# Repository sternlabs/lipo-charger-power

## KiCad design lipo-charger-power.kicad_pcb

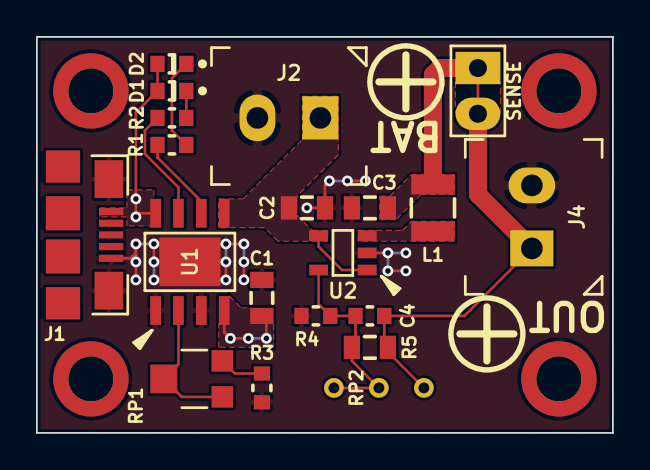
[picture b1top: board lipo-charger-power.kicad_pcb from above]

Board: 2 copper layers, 32.0 x 22.0 mm, 24 parts (0 on the bottom side), 12 nets.

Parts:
C1, C2, C3: 10u; SMD-2012
C4: 18p; SMD-1608
D1: CHRG; SMD-1608-LED
D2: STDBY; SMD-1608-LED
J1: USB-MICROB; USB-MICRO-B-FCI-10118192
J2: BAT; TERM-2-3.5-PTH
J3: SENSE; HEADER-1x2
J4: VREG; TERM-2-3.5-PTH
L1: 2.2u; SMD-2520
MH1, MH2, MH3, MH4: MOUNTHOLE; HOLE-M2.5-COND
R1, R2: 1k; SMD-1608
R3: 1k 1%; SMD-1608
R4: 255k 1%; SMD-1608
R5: 1.15M 1%; SMD-2012
RP1: 20k 25%; SMD-POT-3831
RP2: 2M 10%; POT-3296W
U1: TP4056; SOIC-8-N-EP
U2: NCP1529; SOT-23-5

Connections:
/BAT: C2.1, J2.1, U1.5, U2.1, U2.4
/VREG: C3.1, C4.2, J3.1, J3.2, J4.1, L1.2, R5.1, RP2.1
/VUSB: C1.1, D1.A, D2.A, J1.1, U1.4, U1.8
unnamed: C4.1, R4.1, R5.2, RP2.3, RP2.WIPE, U2.5
unnamed: D1.C, R2.1
unnamed: D2.C, R1.1
unnamed: L1.1, U2.3
unnamed: R1.2, U1.6
unnamed: R2.2, U1.7
unnamed: R3.1, RP1.3
unnamed: RP1.1, RP1.WIPE, U1.2
PGND: C1.2, C2.2, C3.2, J1.5, J1.SHIE, J2.2, J4.2, R3.2, R4.2, U1.1, U1.3, U1.PAD, U2.2

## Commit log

2015-04-24 start
2015-04-24 schematic done
2015-04-25 add layout
2015-04-27 small size changes
2015-04-27 fab outputs from 7cbc2662
2015-04-27 add part numbers
2015-04-27 ignore .net files
2015-04-27 add NCP1529 part number
